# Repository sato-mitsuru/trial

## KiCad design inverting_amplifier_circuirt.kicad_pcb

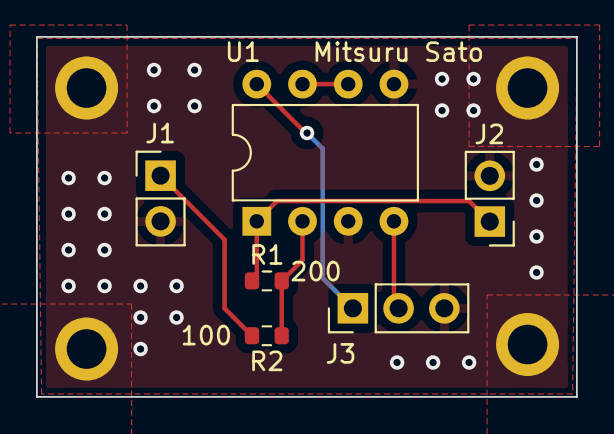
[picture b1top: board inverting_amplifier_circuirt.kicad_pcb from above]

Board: 2 copper layers, 30.0 x 20.0 mm, 10 parts (0 on the bottom side), 7 nets.

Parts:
J1, J2: Conn_01x02_Female; PinHeader_1x02_P2.54mm_Vertical
J3: Conn_01x03_Female; PinHeader_1x03_P2.54mm_Vertical
R1: 200; R_0603_1608Metric
R2: 100; R_0603_1608Metric
REF1, REF2, REF3, REF4: MountingHole_2.2mm_M2_ISO7380_Pad
U1: TL082; DIP-8_W7.62mm

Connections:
+12V: J3.1, U1.8 (V+)
-12V: J3.2, U1.4 (V-)
GND: J1.2, J2.2, J3.3, REF1.1, REF2.1, REF3.1, REF4.1, U1.3 (+), U1.5 (+)
unnamed: J1.1, R2.2
unnamed: J2.1, R1.1, U1.1
unnamed: R1.2, R2.1, U1.2 (-)
unnamed: U1.6 (-), U1.7

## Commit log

2022-12-13 1st commit
